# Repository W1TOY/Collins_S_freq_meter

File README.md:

# Collins S-Line / R390 Frequency Meter

A digital frequency readout for the **Collins S-line** (75S receiver → 32S transmitter) and the **Collins R390** receiver. It has an ESP32 counter board and a 20×4 LCD.

The meter taps the radios' internal oscillator injection lines through high-impedance inputs. It counts each line against a 20 MHz OCXO reference, then calculates the operating (carrier) frequency and shows it, along with the raw oscillator frequencies.

```
W1TOY,  Collins S
IF :    14,455,123      <- HF crystal-oscillator injection (HFO)
VFO:    02,601,450      <- PTO / VFO injection
fc :    11,399,023      <- displayed carrier frequency
```

The repository contains:

| Path | Contents |
|---|---|
| [`fmaster/`](fmaster/) | ESP32 firmware (ESP-IDF v5.4, C) |
| [`PCB/Collins_Freq_Meter/`](PCB/Collins_Freq_Meter/) | KiCad 9 schematic and PCB, PDF plots, and [design notes](PCB/Collins_Freq_Meter/DESIGN_NOTES.md) (BOM, power, connector details) |
| [`CMakeLists.txt`](CMakeLists.txt), [`idf.ps1`](idf.ps1), [`idf.cmd`](idf.cmd), [`.vscode/`](.vscode/) | Lets you build, flash and monitor the firmware from the repository root |

---

## How it works

**Inputs.** Each RF input goes through a 1 nF + 1 kΩ tap into a TLV3502 high-speed comparator. The comparator squares the signal up into 3.3 V logic for the ESP32.
- The two S-line lines (VFO and HFO) are **pass-through**: the coax from the 75S goes in, and straight out to the 32S. The meter only adds about 1 kΩ / 3 pF of load.
- Sensitivity is about 60 mVpp.

**Counting.** The ESP32 has one hardware pulse counter (PCNT) per input, so every channel is measured at the same time over the same gate.
- The gate is a 2 Hz signal the ESP32 generates itself. It is high for 0.484 s of each 0.5 s period.
- It is looped back from GPIO13 to GPIO12 and enables every counter.
- On the gate's falling edge an interrupt reads and clears all counters.
- **Result:** a new reading every 0.5 s, with about 2 Hz resolution.

**Calibration.** One channel counts a 20 MHz ECS ECOC-7050 OCXO.
- The ratio *nominal 20 MHz / measured* corrects every other channel for the error of the ESP32's own crystal, which sets the gate length.
- The factor is only updated while the reference reads within ±0.1 % of 20 MHz. While the OCXO is unpowered or still warming up, the last good factor is kept (1.0 at power-up).

**Displayed frequency.**

| Mode | Formula |
|---|---|
| Collins S-line | `fc = HFO − VFO − 455 kHz ± 1.35 kHz` |
| Collins R390 | `fc = IF1 − IF2 − VFO − 455 kHz` |

- **S-line BFO correction:** the ±1.35 kHz is the offset of the S-line carrier crystals (453.650 kHz USB, 456.350 kHz LSB).
  - The firmware assumes **LSB below 8 MHz** (+1.35 kHz) and **USB above** (−1.35 kHz), the usual sideband for each band.
  - If you run the opposite sideband, the reading is off by 2.7 kHz (see [Known limitations](#known-limitations)).
- **R390 formula:** carried over from the prototype and not yet verified.

### Inputs and I/O

| Connector | Signal | Range | ESP32 | Firmware channel |
|---|---|---|---|---|
| J2 → J3 (SMA, pass-through) | 75S VFO / PTO injection → 32S | 2.5–2.7 MHz | GPIO27 | CH1 |
| J4 → J5 (SMA, pass-through) | 75S HF crystal-oscillator injection → 32S | ~6.9–33 MHz | GPIO32 | CH5 (direct, or ÷2 via JP1) |
| J9 (SMA) | R390 IF1 | ≤ ~30 MHz | GPIO26 | CH2 |
| J10 (SMA) | R390 IF2 | ≤ ~30 MHz | GPIO25 | CH3 |
| J11 (SMA) | R390 VFO | ≤ ~30 MHz | GPIO33 | CH4 |
| Y1 (on board) | 20 MHz OCXO reference | 20 MHz | GPIO14 | CH0 |
| JP2 (open) | 1 MHz self-test loopback, GPIO15 → GPIO2 | 1 MHz | GPIO2 | CH6 |
| J12 / J7 pin 5 | PTT sense (through a 2N7000 stage) | DC | GPIO4 | — |
| J7 pins 2–4 | Mode selector SEL0 / SEL1 / SEL2 (active low) | — | GPIO18 / 19 / 21 | — |
| J6 | 20×4 LCD, PCF8574 I2C backpack at 0x27 (via 2N7000 level shifter) | — | GPIO16 SDA / GPIO17 SCL | — |
| J1 | 12 V DC (10–18 V), centre positive | — | — | — |

The S-line uses RCA connectors, so you need SMA-male-to-RCA-male cables (RG-174 or RG-316).

---

## Operating instructions

### 1. Connect

1. **S-line:** break the two injection cables between the 75S and the 32S and route them through the meter.
   - 75S **VFO out** → **J2**, then **J3** → 32S VFO in.
   - 75S **HFO out** → **J4**, then **J5** → 32S HFO in.
2. **R390 (optional):** connect IF1 → **J9**, IF2 → **J10** and VFO → **J11**.
   - These inputs are high impedance.
   - Fit R28 / R35 / R42 (51 Ω) only if the source needs a 50 Ω termination.
3. **PTT (needed only for mode 2):** connect the station keying line to **J12** (or J7 pin 5).
   - **JP9 open** (default): a keying *voltage* of 4–30 V on PTT_IN means TX.
   - **JP9 fitted:** a *contact closure to ground* means TX. You must also set `PTT_TX_LEVEL` to `1` in [`main.c`](fmaster/main/main.c) and rebuild.
4. **LCD:** plug it into **J6** (GND, VCC 5 V, SDA, SCL). Check your backpack's pin order first.
5. **Power:** 12 V DC (the station 13.8 V supply is fine) into **J1**.
   - It draws about 1 A for the first minute while the OCXO oven warms up, then about 0.35 A.
   - **The 7805 needs a heatsink** of 10 °C/W or better.

### 2. Choose the mode

The mode is read from a selector switch on J7 (SEL0–SEL2; pull the selected line to GND). It is checked every 200 ms, so you can change it while the meter is running.

| Selector | Mode | Display |
|---|---|---|
| SEL0 (GPIO18) | **0: Collins S-line** (75S → 32S) | header `Collins S`; IF = HFO, VFO = VFO, fc = S-line carrier |
| SEL1 (GPIO19) | **1: Collins R390** | header `Collins R390`; IF = IF1, VFO = VFO, fc = R390 frequency |
| SEL2 (GPIO21) | **2: R390 receive / 32S transmit** | follows PTT: shows the R390 display on receive and the S-line display while transmitting |
| none | — | `select mode`; frequencies are still logged on the serial port |

- **JP3 is bridged by default.** It grounds SEL0, so the board starts in S-line mode with no switch fitted.
  - SEL0 takes priority over the other positions, so **remove JP3 when you fit a selector switch**. Otherwise the meter stays in S-line mode.

### 3. Power up and read

- The display shows the header, then a fresh reading every 0.5 s.
- **During the first minute or so,** the OCXO is still warming up. Frequencies are then only as accurate as the ESP32's own crystal, about ±20 ppm, until the reference settles.
- Once the reference is in range, the serial log shows `reference OK (… Hz) - calibration active`.
- If the reference drops out of range, the log shows `reference … Hz out of range - keeping the last calibration factor`.

### 4. Serial monitor

The firmware prints every channel twice a second: the raw value and the OCXO-calibrated value.

```
f[0]=19999987 cal=20000000  f[1]=2601449 cal=2601450  ...  f[6]=1000001 cal=1000001
```

| Index | Channel |
|---|---|
| 0 | reference |
| 1 | 75S VFO |
| 2 | R390 IF1 |
| 3 | R390 IF2 |
| 4 | R390 VFO |
| 5 | 75S HFO |
| 6 | self-test |

Use **ESP32: Monitor** in VS Code or `.\idf monitor` (see below). Press **Ctrl+]** to leave the monitor.

### 5. Self-test

Fit **JP2**. This loops the ESP32's internal 1 MHz test output (GPIO15) back into channel 6 (GPIO2). `f[6]` should then read about 1,000,000 Hz in the serial log, which confirms the gate and counter chain without any radio connected.

### USB-only operation

The ESP32 can run from its USB port alone, for programming or bench tests. In that case the OCXO is unpowered: the reference reads 0 and calibration stays off.

**JP6** links the board's 5 V to the DevKit's VIN pin. Some DevKit clones lack the USB-VBUS protection diode. On those, **remove JP6 before connecting USB while 12 V is applied**, so the board's 5 V can't feed back into your PC. The [design notes](PCB/Collins_Freq_Meter/DESIGN_NOTES.md#power-single-12-v-input) explain how to check your DevKit.

---

## Building and flashing the firmware

The build has been tested on Windows with ESP-IDF v5.4 and the Espressif VS Code extension. Everything runs from the **repository root**; you never need to `cd` into `fmaster/`.

- The root [`CMakeLists.txt`](CMakeLists.txt) points ESP-IDF at `fmaster/main` and `fmaster/sdkconfig`.
- Build output goes to `fmaster/build/`.

### Prerequisites

- [ESP-IDF v5.4](https://docs.espressif.com/projects/esp-idf/en/v5.4/esp32/get-started/).
- VS Code with the [ESP-IDF extension](https://marketplace.visualstudio.com/items?itemName=espressif.esp-idf-extension) (optional, but gives the status-bar buttons).
- **Machine-specific paths:** [`.vscode/settings.json`](.vscode/settings.json) and [`idf.ps1`](idf.ps1) hold the paths of the original development machine. Change these to match your install:
  - `C:\Users\email\esp\v5.4\esp-idf` (ESP-IDF)
  - `C:\Users\email\.espressif` (tools)
  - the serial port, `COM3`

### Option A: VS Code

Open the repository folder (**File → Open Folder**). Then use any of these:
- **ESP-IDF status-bar buttons:** set target, choose port, menuconfig, full clean, build, flash, monitor.
- **Ctrl+Shift+B** to build.
- **Terminal → Run Task**: ESP32 Build, Flash, Flash + Monitor, Monitor, Menuconfig, Full Clean.

### Option B: command line

From PowerShell or cmd in the repository root:

```powershell
.\idf build                  # compile
.\idf flash monitor          # flash, then open the serial monitor
.\idf -Port COM5 flash       # use a different serial port (default COM3, or set ESPPORT)
.\idf menuconfig             # ESP-IDF configuration
.\idf fullclean              # delete the build
```

`idf.ps1` loads the ESP-IDF environment by itself, so no special "ESP-IDF terminal" is needed.

### Firmware options

These are at the top of [`fmaster/main/main.c`](fmaster/main/main.c):

| Define | Default | Purpose |
|---|---|---|
| `FREQ_REF_OSCILLATOR_HZ` | `20000000.0` | Nominal OCXO frequency. For best absolute accuracy, put the value you measured against a good standard here (the OCXO is within ±500 ppb when delivered). |
| `HFO_PRESCALE` | `1` | Set to `2` if JP1 is moved to ÷2 (the HFO input then goes through the 74LVC74A). |
| `PCNT_GLITCH_FILTER_NS` | `0` | Counter glitch filter. Leave it off: a 30 ns filter blocks the 20 MHz reference and any HFO above about 16 MHz. |
| `PTT_TX_LEVEL` | `0` | GPIO4 level that means TX. `0` for voltage keying (JP9 open), `1` for contact closure (JP9 fitted). |
| `ENABLE_LCD_DISPLAY` | defined | Comment it out to run without an LCD (serial log only). |
| `show_moving_average` / `num_moving_average` | `0` / `2` | Optional moving average over the last N readings (N up to 16). |

The LCD's I2C address is set in [`fmaster/main/i2c-lcd.c`](fmaster/main/i2c-lcd.c). It is `0x27` for a PCF8574; use `0x3F` for a PCF8574A.

---

## Building the board

The PCB is a 100 × 150 mm, two-sided board laid out for CNC milling. Almost every part is through-hole. The SMD exceptions are the TLV3502 comparators (SOIC-8), the 74LVC74A (SOIC-14) and the OCXO.

- [Schematic (PDF)](PCB/Collins_Freq_Meter/Collins_Freq_Meter_schematic.pdf)
- [Placement (PDF)](PCB/Collins_Freq_Meter/Collins_Freq_Meter_placement.pdf)
- [Top copper (PDF)](PCB/Collins_Freq_Meter/Collins_Freq_Meter_route_top.pdf)
- [Bottom copper (PDF)](PCB/Collins_Freq_Meter/Collins_Freq_Meter_route_bottom.pdf)
- [Top silkscreen (PDF)](PCB/Collins_Freq_Meter/Collins_Freq_Meter_silk_top.pdf)

The [design notes](PCB/Collins_Freq_Meter/DESIGN_NOTES.md) have the full BOM, power budget, heatsinking, connector pinouts and footprint checks. Two things matter on a milled (unplated) board:
- each of the 22 vias needs a wire soldered through it;
- through-hole pads with tracks on both sides must be soldered on both sides.

---

## Known limitations

- **S-line sideband.** The ±1.35 kHz BFO correction is chosen by frequency (LSB below 8 MHz), not by the 75S sideband switch. Running the opposite sideband reads 2.7 kHz off.
- **R390 formula.** `IF1 − IF2 − VFO − 455 kHz` is carried over from the prototype and still needs checking against the R390 frequency scheme. IF2 is measured, but it has no line of its own on the LCD; it appears only in the serial log.
- **Mode names in the serial log.** Mode 2 is labelled `Reserved` there, although it is the R390-receive / 32S-transmit mode.

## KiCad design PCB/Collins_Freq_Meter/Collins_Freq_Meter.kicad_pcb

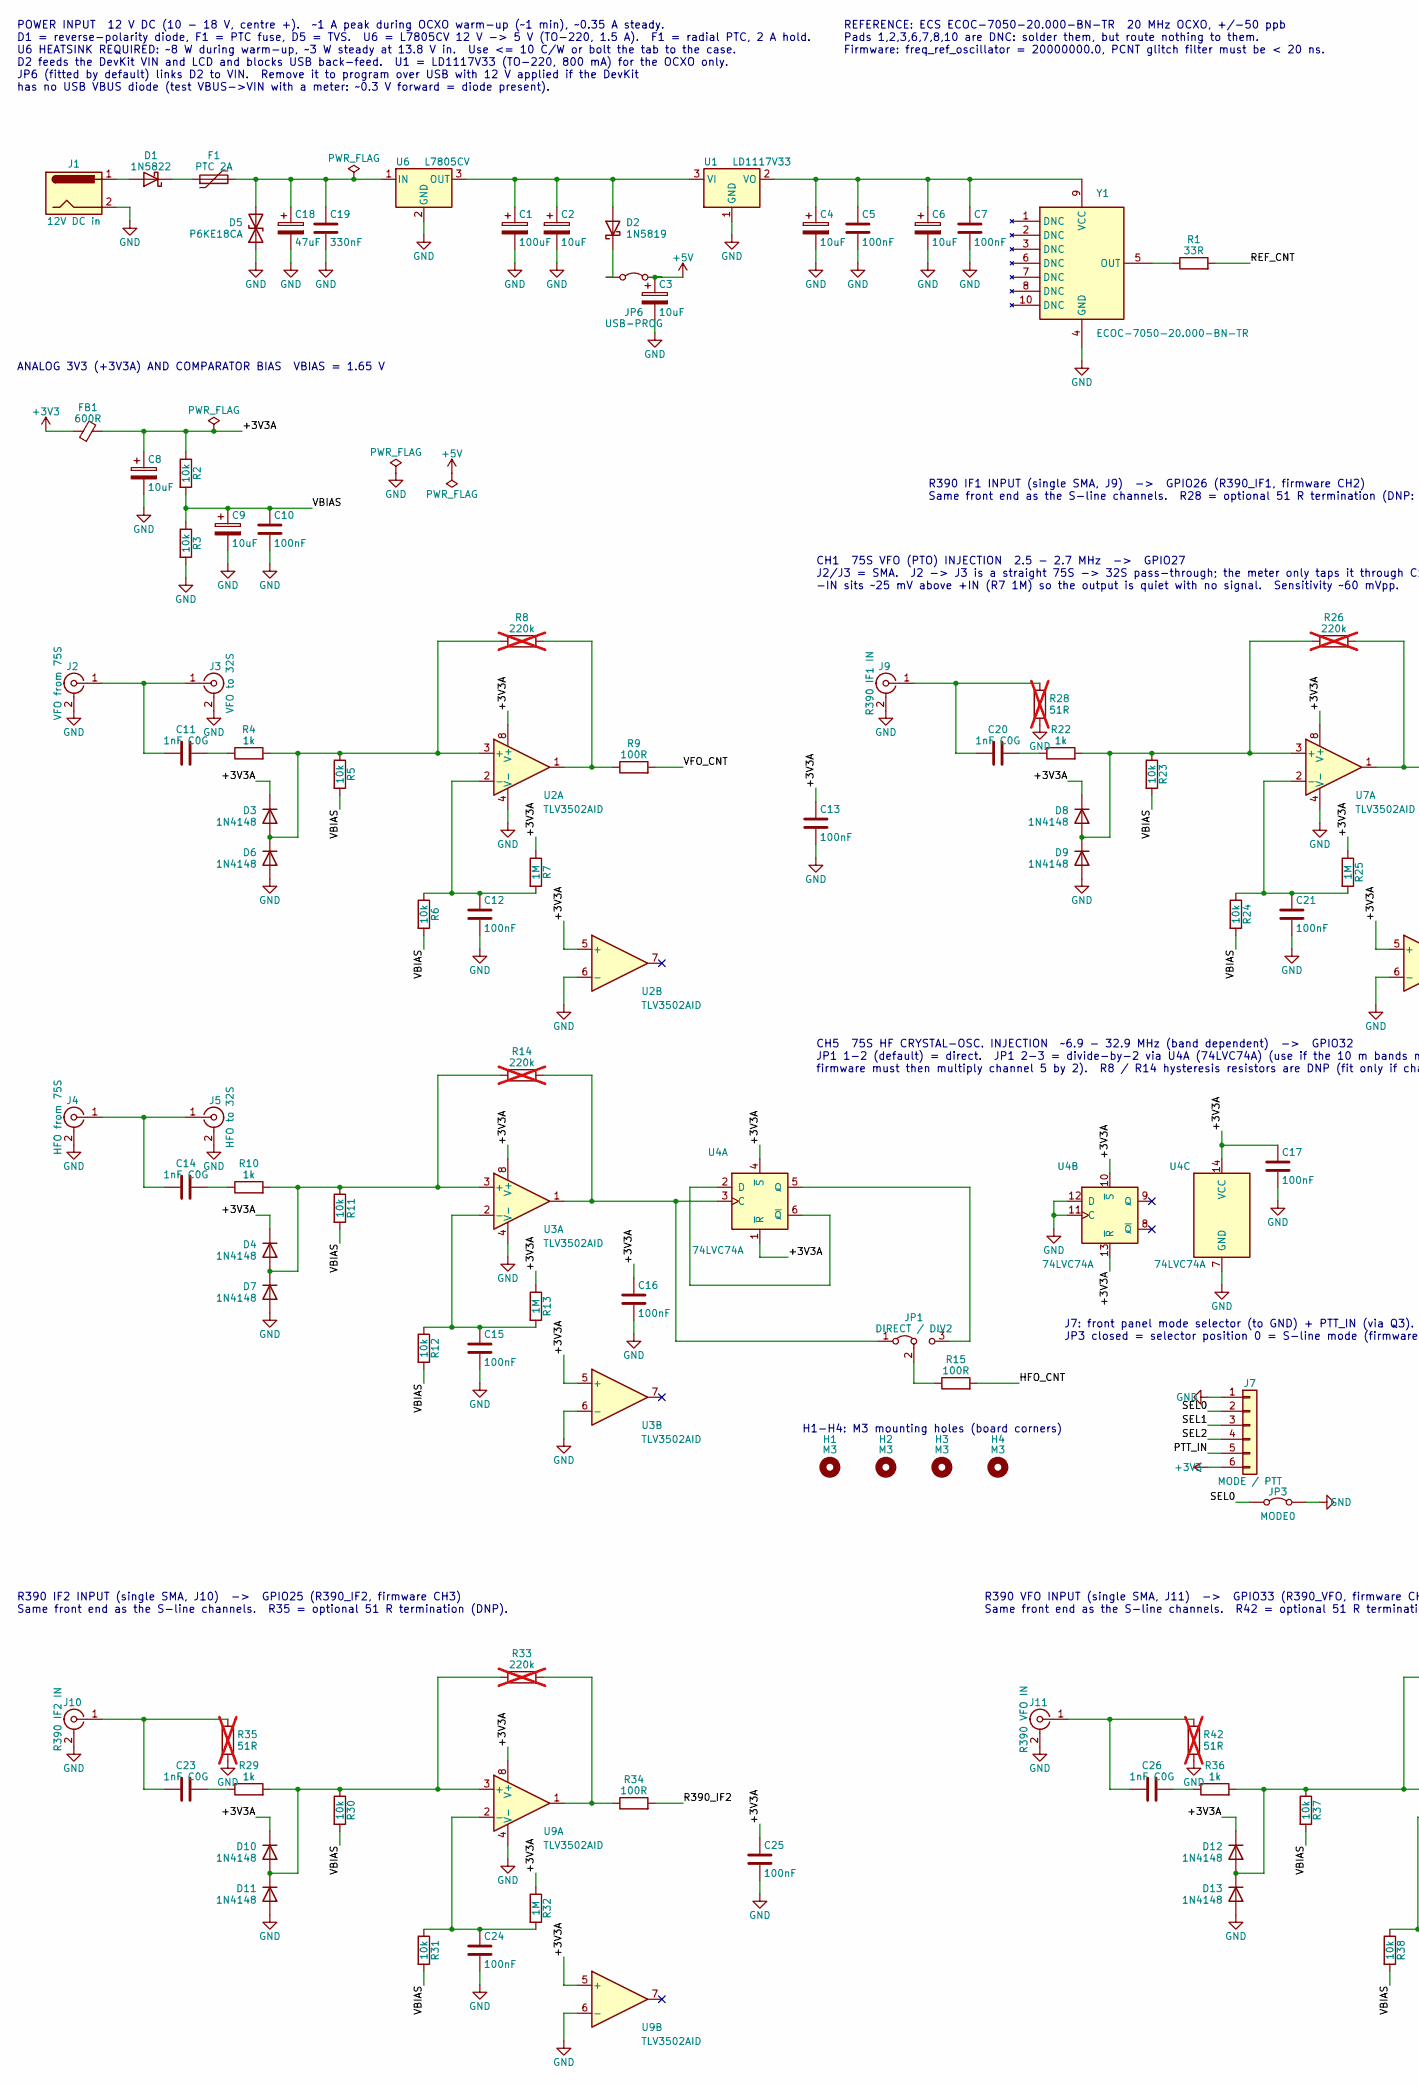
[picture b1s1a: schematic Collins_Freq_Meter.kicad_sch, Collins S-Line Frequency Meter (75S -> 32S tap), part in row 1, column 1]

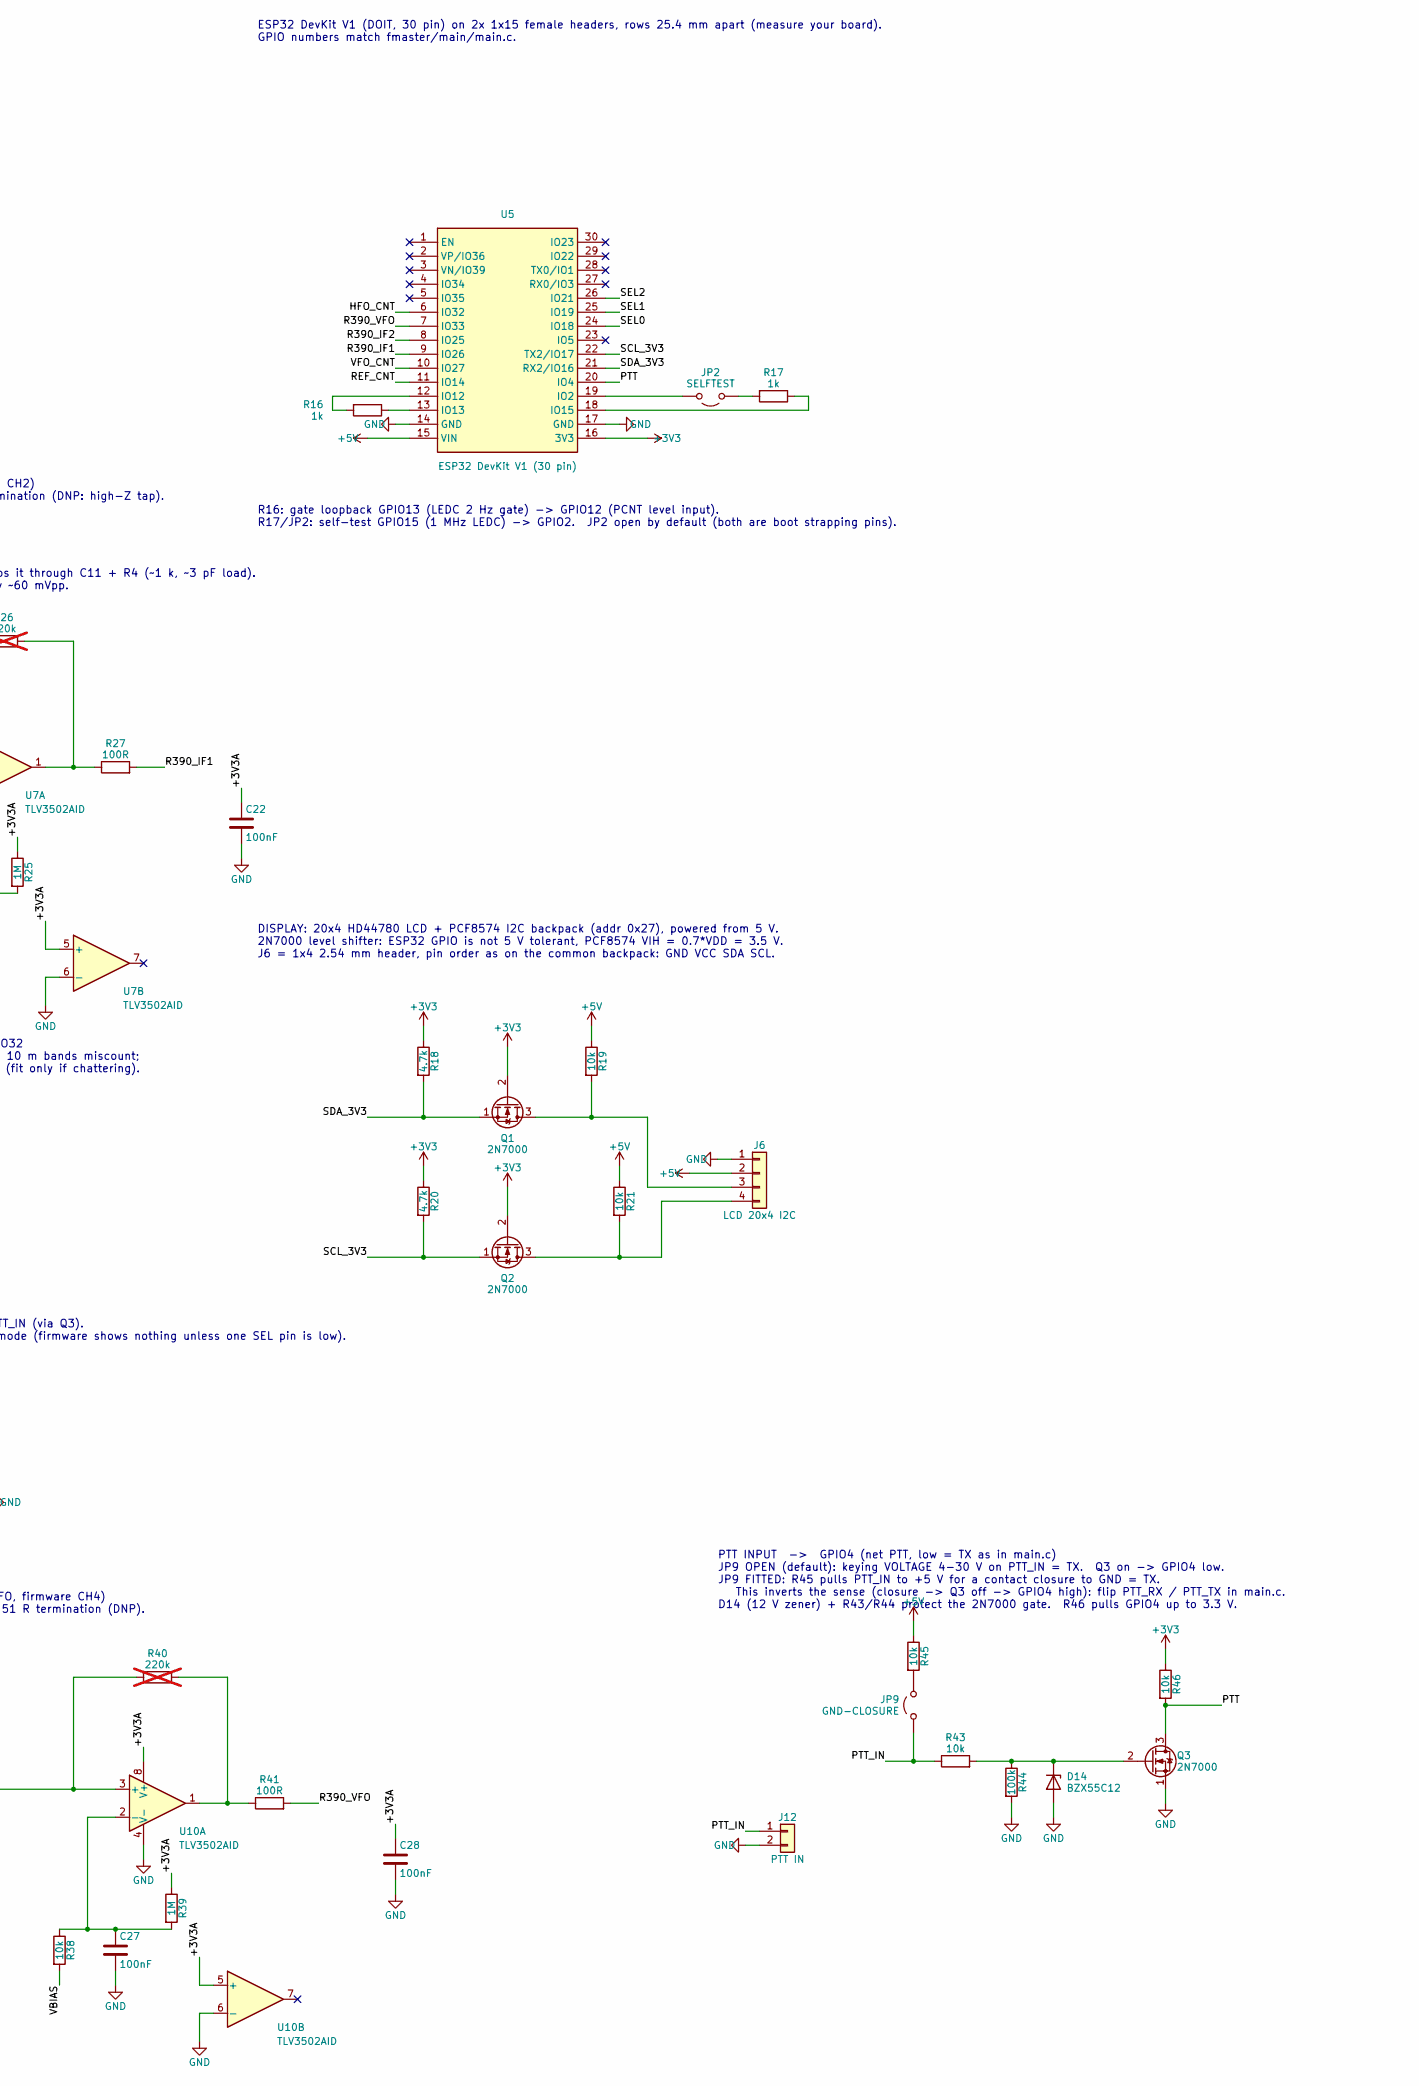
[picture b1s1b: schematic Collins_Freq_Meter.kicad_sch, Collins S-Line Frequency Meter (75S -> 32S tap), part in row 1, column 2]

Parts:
C1: 100uF; CP_Radial_D6.3mm_P2.50mm
C2, C3, C4, C6, C8, C9: 10uF; CP_Radial_D5.0mm_P2.00mm
C5, C7, C10, C12, C13, C15, C16, C17, C21, C22, C24, C25, C27, C28: 100nF; C_Disc_D5.0mm_W2.5mm_P5.00mm
C11, C14, C20, C23, C26: 1nF C0G; C_Disc_D5.0mm_W2.5mm_P5.00mm
C18: 47uF; CP_Radial_D6.3mm_P2.50mm
C19: 330nF; C_Disc_D5.0mm_W2.5mm_P5.00mm
D1: 1N5822; D_DO-201AD_P15.24mm_Horizontal
D2: 1N5819; D_DO-41_SOD81_P10.16mm_Horizontal
D3, D4, D6, D7, D8, D9, D10, D11, D12, D13: 1N4148; D_DO-35_SOD27_P7.62mm_Horizontal
D5: P6KE18CA; D_DO-15_P10.16mm_Horizontal
D14: BZX55C12; D_DO-35_SOD27_P7.62mm_Horizontal
F1: PTC 2A; Fuse_Bourns_MF-RHT200
FB1: 600R; L_Axial_L5.3mm_D2.2mm_P10.16mm_Horizontal_Vishay_IM-1
H1, H2, H3, H4: M3; MountingHole_3.2mm_M3
J1: 12V DC in; BarrelJack_CUI_PJ-102AH_Horizontal
J2: VFO from 75S; SMA_Amphenol_132134_Vertical
J3: VFO to 32S; SMA_Amphenol_132134_Vertical
J4: HFO from 75S; SMA_Amphenol_132134_Vertical
J5: HFO to 32S; SMA_Amphenol_132134_Vertical
J6: LCD 20x4 I2C; PinHeader_1x04_P2.54mm_Vertical
J7: MODE / PTT; PinHeader_1x06_P2.54mm_Vertical
J9: R390 IF1 IN; SMA_Amphenol_132134_Vertical
J10: R390 IF2 IN; SMA_Amphenol_132134_Vertical
J11: R390 VFO IN; SMA_Amphenol_132134_Vertical
J12: PTT IN; PinHeader_1x02_P2.54mm_Vertical
JP1: DIRECT / DIV2; PinHeader_1x03_P2.54mm_Vertical
JP2: SELFTEST; PinHeader_1x02_P2.54mm_Vertical
JP3: MODE0; PinHeader_1x02_P2.54mm_Vertical
JP6: USB-PROG; PinHeader_1x02_P2.54mm_Vertical
JP9: GND-CLOSURE; PinHeader_1x02_P2.54mm_Vertical
Q1, Q2, Q3: 2N7000; TO-92_Inline_Wide
R1: 33R; R_Axial_DIN0207_L6.3mm_D2.5mm_P10.16mm_Horizontal
R2, R3, R5, R6, R11, R12, R19, R21, R23, R24, R30, R31, R37, R38, R43, R45, R46: 10k; R_Axial_DIN0207_L6.3mm_D2.5mm_P10.16mm_Horizontal
R4, R10, R16, R17, R22, R29, R36: 1k; R_Axial_DIN0207_L6.3mm_D2.5mm_P10.16mm_Horizontal
R7, R13, R25, R32, R39: 1M; R_Axial_DIN0207_L6.3mm_D2.5mm_P10.16mm_Horizontal
R8, R14, R26, R33, R40: 220k; R_Axial_DIN0207_L6.3mm_D2.5mm_P10.16mm_Horizontal; not fitted
R9, R15, R27, R34, R41: 100R; R_Axial_DIN0207_L6.3mm_D2.5mm_P10.16mm_Horizontal
R18, R20: 4.7k; R_Axial_DIN0207_L6.3mm_D2.5mm_P10.16mm_Horizontal
R28, R35, R42: 51R; R_Axial_DIN0207_L6.3mm_D2.5mm_P10.16mm_Horizontal; not fitted
R44: 100k; R_Axial_DIN0207_L6.3mm_D2.5mm_P10.16mm_Horizontal
U1: LD1117V33; TO-220-3_Vertical
U2, U3, U7, U9, U10: TLV3502AID; SOIC-8_3.9x4.9mm_P1.27mm
U4: 74LVC74A; SOIC-14_3.9x8.7mm_P1.27mm
U5: ESP32 DevKit V1 (30 pin); ESP32-DevKit-V1_30pin_2x15_P2.54mm_W25.4mm
U6: L7805CV; TO-220-3_Vertical
Y1: ECOC-7050-20.000-BN-TR; ECS_ECOC-7050_7.0x5.0mm

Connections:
+3V3: FB1.1, J7.6, Q1.2 (G), Q2.2 (G), R18.1, R20.1, R46.1, U5.16 (3V3)
+5V: C3.1, J6.2, JP6.2 (B), R19.1, R21.1, R45.1, U5.15 (VIN)
/+3V3A: C8.1, C13.1, C16.1, C17.1, C22.1, C25.1, C28.1, D3.1 (K), D4.1 (K), D8.1 (K), D10.1 (K), D12.1 (K), FB1.2, R2.1, R7.1, R13.1, R25.1, R32.1, R39.1, U2.5 (+), U2.8 (V+), U3.5 (+), U3.8 (V+), U4.1 (~R), U4.4 (~S), U4.10 (~S), U4.13 (~R), U4.14 (VCC), U7.5 (+), U7.8 (V+), U9.5 (+), U9.8 (V+), U10.5 (+), U10.8 (V+)
/HFO_CNT: R15.2, U5.6 (IO32)
/PTT: Q3.3 (D), R46.2, U5.20 (IO4)
/PTT_IN: J7.5, J12.1, JP9.1 (A), R43.1
/R390_IF1: R27.2, U5.9 (IO26)
/R390_IF2: R34.2, U5.8 (IO25)
/R390_VFO: R41.2, U5.7 (IO33)
/REF_CNT: R1.2, U5.11 (IO14)
/SCL_3V3: Q2.1 (S), R20.2, U5.22 (TX2/IO17)
/SDA_3V3: Q1.1 (S), R18.2, U5.21 (RX2/IO16)
/SEL0: J7.2, JP3.1 (A), U5.24 (IO18)
/SEL1: J7.3, U5.25 (IO19)
/SEL2: J7.4, U5.26 (IO21)
/VBIAS: C9.1, C10.1, R2.2, R3.1, R5.2, R6.2, R11.2, R12.2, R23.2, R24.2, R30.2, R31.2, R37.2, R38.2
/VFO_CNT: R9.2, U5.10 (IO27)
GND: C1.2, C2.2, C3.2, C4.2, C5.2, C6.2, C7.2, C8.2, C9.2, C10.2, C12.2, C13.2, C15.2, C16.2, C17.2, C18.2, C19.2, C21.2, C22.2, C24.2, C25.2, C27.2, C28.2, D5.1 (A1), D6.2 (A), D7.2 (A), D9.2 (A), D11.2 (A), D13.2 (A), D14.2 (A), J1.2, J2.2 (Ext), J3.2 (Ext), J4.2 (Ext), J5.2 (Ext), J6.1, J7.1, J9.2 (Ext), J10.2 (Ext), J11.2 (Ext), J12.2, JP3.2 (B), Q3.1 (S), R3.2, R28.2, R35.2, R42.2, R44.2, U1.1 (GND), U2.4 (V-), U2.6 (-), U3.4 (V-), U3.6 (-), U4.7 (GND), U4.11 (C), U4.12 (D), U5.14 (GND), U5.17 (GND), U6.2 (GND), U7.4 (V-), U7.6 (-), U9.4 (V-), U9.6 (-), U10.4 (V-), U10.6 (-), Y1.4 (GND)
unnamed: C11.2, R4.1
unnamed: C14.2, R10.1
unnamed: C20.2, R22.1
unnamed: C23.2, R29.1
unnamed: C26.2, R36.1
unnamed: D1.2 (A), J1.1
unnamed: D1.1 (K), F1.1
unnamed: C1.1, C2.1, D2.2 (A), U1.3 (VI), U6.3 (OUT)
unnamed: D2.1 (K), JP6.1 (A)
unnamed: D3.2 (A), D6.1 (K), R4.2, R5.1, R8.2, U2.3 (+)
unnamed: D4.2 (A), D7.1 (K), R10.2, R11.1, R14.2, U3.3 (+)
unnamed: C18.1, C19.1, D5.2 (A2), F1.2, U6.1 (IN)
unnamed: D8.2 (A), D9.1 (K), R22.2, R23.1, R26.2, U7.3 (+)
unnamed: D10.2 (A), D11.1 (K), R29.2, R30.1, R33.2, U9.3 (+)
unnamed: D12.2 (A), D13.1 (K), R36.2, R37.1, R40.2, U10.3 (+)
unnamed: D14.1 (K), Q3.2 (G), R43.2, R44.1
unnamed: C11.1, J2.1 (In), J3.1 (In)
unnamed: C14.1, J4.1 (In), J5.1 (In)
unnamed: J6.3, Q1.3 (D), R19.2
unnamed: J6.4, Q2.3 (D), R21.2
unnamed: C20.1, J9.1 (In), R28.1
unnamed: C23.1, J10.1 (In), R35.1
unnamed: C26.1, J11.1 (In), R42.1
unnamed: JP1.1 (A), R14.1, U3.1, U4.3 (C)
unnamed: JP1.3 (B), U4.5 (Q)
unnamed: JP1.2 (C), R15.1
unnamed: JP2.1 (A), R17.2
unnamed: JP2.2 (B), U5.19 (IO2)
unnamed: JP9.2 (B), R45.2
unnamed: R8.1, R9.1, U2.1
unnamed: R26.1, R27.1, U7.1
unnamed: R33.1, R34.1, U9.1
unnamed: R40.1, R41.1, U10.1
unnamed: C4.1, C5.1, C6.1, C7.1, U1.2 (VO), Y1.9 (VCC)
unnamed: C12.1, R6.1, R7.2, U2.2 (-)
unnamed: C15.1, R12.1, R13.2, U3.2 (-)
unnamed: U4.2 (D), U4.6 (~Q)
unnamed: R16.2, U5.12 (IO12)
unnamed: R16.1, U5.13 (IO13)
unnamed: R17.1, U5.18 (IO15)
unnamed: C21.1, R24.1, R25.2, U7.2 (-)
unnamed: C24.1, R31.1, R32.2, U9.2 (-)
unnamed: C27.1, R38.1, R39.2, U10.2 (-)
unnamed: R1.1, Y1.5 (OUT)

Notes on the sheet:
POWER INPUT 12 V DC (10 - 18 V, centre +). ~1 A peak during OCXO warm-up (~1 min), ~0.35 A steady. D1 = reverse-polarity diode, F1 = PTC fuse, D5 = TVS. U6 = L7805CV 12 V -> 5 V (TO-220, 1.5 A). F1 = radial PTC, 2 A hold. U6 HEATSINK REQUIRED: ~8 W during warm-up, ~3 W steady at 13.8 V in. Use <= 1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
REFERENCE: ECS ECOC-7050-20.000-BN-TR 20 MHz OCXO, +/-50 ppb Pads 1,2,3,6,7,8,10 are DNC: solder them, but route nothing to them. Firmware: freq_ref_oscillator = 20000000.0, PCNT glitch filter must be < 20 ns.
ANALOG 3V3 (+3V3A) AND COMPARATOR BIAS VBIAS = 1.65 V
CH1 75S VFO (PTO) INJECTION 2.5 - 2.7 MHz -> GPIO27 J2/J3 = SMA. J2 -> J3 is a straight 75S -> 32S pass-through; the meter only taps it through C11 + R4 (~1 k, ~3 pF load). -IN sits ~25 mV above +IN (R7 1M) so the output is quiet with no signal. Sensitivity ~60 mVpp.
R390 IF1 INPUT (single SMA, J9) -> GPIO26 (R390_IF1, firmware CH2) Same front end as the S-line channels. R28 = optional 51 R termination (DNP: high-Z tap).
CH5 75S HF CRYSTAL-OSC. INJECTION ~6.9 - 32.9 MHz (band dependent) -> GPIO32 JP1 1-2 (default) = direct. JP1 2-3 = divide-by-2 via U4A (74LVC74A) (use if the 10 m bands miscount; firmware must then multiply channel 5 by 2). R8 / R14 hysteresis resistors are DNP (fit only if chattering).
R390 IF2 INPUT (single SMA, J10) -> GPIO25 (R390_IF2, firmware CH3) Same front end as the S-line channels. R35 = optional 51 R termination (DNP).
R390 VFO INPUT (single SMA, J11) -> GPIO33 (R390_VFO, firmware CH4) Same front end as the S-line channels. R42 = optional 51 R termination (DNP).
PTT INPUT -> GPIO4 (net PTT, low = TX as in main.c) JP9 OPEN (default): keying VOLTAGE 4-30 V on PTT_IN = TX. Q3 on -> GPIO4 low. JP9 FITTED: R45 pulls PTT_IN to +5 V for a contact closure to GND = TX. This inverts the sense (closure -> Q3 off -> GPIO4 high): flip PTT_RX / PTT_TX in main.c. D14 (12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
ESP32 DevKit V1 (DOIT, 30 pin) on 2x 1x15 female headers, rows 25.4 mm apart (measure your board). GPIO numbers match fmaster/main/main.c.
R16: gate loopback GPIO13 (LEDC 2 Hz gate) -> GPIO12 (PCNT level input). R17/JP2: self-test GPIO15 (1 MHz LEDC) -> GPIO2. JP2 open by default (both are boot strapping pins).
DISPLAY: 20x4 HD44780 LCD + PCF8574 I2C backpack (addr 0x27), powered from 5 V. 2N7000 level shifter: ESP32 GPIO is not 5 V tolerant, PCF8574 VIH = 0.7*VDD = 3.5 V. J6 = 1x4 2.54 mm header, pin order as on the common backpack: GND VCC SDA SCL.
J7: front panel mode selector (to GND) + PTT_IN (via Q3). JP3 closed = selector position 0 = S-line mode (firmware shows nothing unless one SEL pin is low).
H1-H4: M3 mounting holes (board corners)

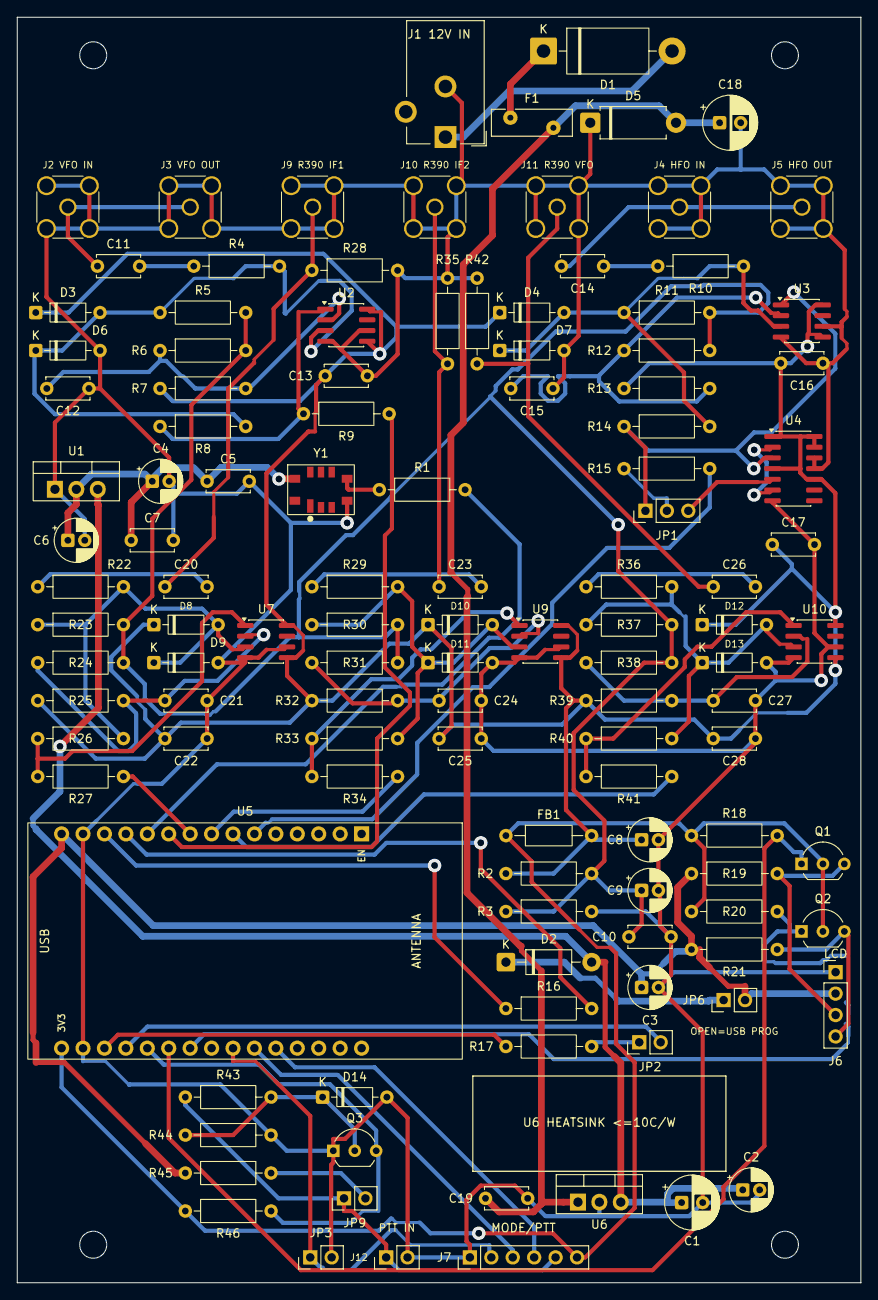
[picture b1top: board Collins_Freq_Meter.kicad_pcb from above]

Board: 2 copper layers, 100.0 x 150.0 mm, 123 parts (0 on the bottom side), 62 nets.

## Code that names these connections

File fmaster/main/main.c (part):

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 *    is a calibration factor that removes the error of the ESP32's own crystal (it times the gate).
 *
 * Board: Collins_Freq_Meter (KiCad project in ../PCB/Collins_Freq_Meter)
 *   GPIO14  REF_CNT   20 MHz ECOC-7050 OCXO (via R1)
 *   GPIO27  CH1       75S VFO / PTO injection (2.5-2.7 MHz)
 *   GPIO26  CH2       R390 IF1   (J9)
 *   GPIO25  CH3       R390 IF2   (J10)
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 *   GPIO15            1 MHz self-test output (LEDC channel 1)
 *   GPIO16 / GPIO17   I2C SDA / SCL to the 20x4 LCD (PCF8574 backpack, via 2N7000 level shifter)
 *   GPIO18/19/21      mode selector positions 0/1/2 (active low, JP3 grounds position 0)
 *   GPIO4             PTT sense (Q3 2N7000 pulls it low on TX)
 */
#include <stdio.h>
#include <string.h>
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 * Set to e.g. 13 (= 1 APB cycle) only if a channel picks up glitches. 0 = filter disabled. */
#define PCNT_GLITCH_FILTER_NS   0

/* PTT sense polarity on GPIO4. Q3 pulls GPIO4 low when PTT_IN carries the keying voltage (JP9 open),
 * so TX = low. With JP9 fitted (contact closure to GND = TX) the sense is inverted: set this to 1. */
#define PTT_TX_LEVEL            0

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
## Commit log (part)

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2024-10-28 multi counter works
